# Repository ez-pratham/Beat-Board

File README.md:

# BEAT BOARD

**BEAT BOARD** is a handheld music device and synthesizer that has a cyber-retro look and feel. It is built around the dual-core **ESP32** microcontroller. It has four gold-plated touch pads that are used for finger drumming and for playing brass lead notes. It also has a 3.5" color screen that shows an audio interface in real time. There is a $2 \times 2$ control pad for master control. There is also an onboard MAX98357A I2S Class-D amplifier that powers a speaker with a cavity design.

When the **MODE** button is pressed, a menu appears on the screen. This menu allows the user to switch between a **808 Drum Machine** that has a live 16-step sequencer and a **4-Valve Acoustic Trumpet Brass Synth** that has moving valve pistons and soundwave flares!

---

## Photos & Screenshots

### Top View (Silkscreen Doodles & Controls)

### Bottom View (ROG "BEAT BOARD" & Punk Doodles)

### Schematic
  
*(Vector PDF available at [docs/images/schematic.pdf](./docs/images/schematic.pdf) | Vector SVG at [docs/images/schematic_diagram.svg](./docs/images/schematic_diagram.svg))*

### PCB Board Layout
#### Top Layer Layout (Orthogonal SPI/I2S Routing & Ground Plane)

#### Bottom Layer Layout (Power Rails & Ground Plane)

---
---

## How It Works

### How the parts fit on the console

I laid out every section of the carrier board to make the console as comfortable as possible for fast finger drumming and trumpet solos:

1. **Center Top (Display)**: A **3.5" Color TFT LCD module (480x320 SPI)** is raised at the center of the console. It shows audio waveforms, the 16-step drum sequencer grid, BPM tempo, battery status, and the interactive instrument selection menu.

2. **Center Core (Microcontroller)**: An **ESP32-WROOM-32 DevKit** microcontroller sits in female socket headers directly below the display. Its USB-C port faces downwards at the bottom edge, making firmware flashing and USB power convenient.

3. **Left Wing (Master Navigation & Drum Pads)**:
   - **Master Control Pad (Top Left)**: A $2 \times 2$ grid of tactile buttons (`UP`, `DOWN`, `SELECT`, `MODE`) lets your left thumb navigate menus, change kits, shift octaves, or mute the horn without lifting your hands.
   - **Left Touch Pads (Bottom Left)**: Two $24 \times 24\text{ mm}$ gold-plated capacitive touch pads (`PAD 1: KICK / Bb3` and `PAD 2: SNARE / D4`) are driven by two small red TTP223 daughterboards.

4. **Dedicated Top-Right Audio Bay**:
   - The **MAX98357A I2S 3W Class-D amplifier module** and green **KF301 2-pin speaker terminal block** are set in the isolated top-right corner.
   - Twisted red and black speaker wires leave cleanly from the top-right edge to a 3W cavity speaker, fully removed from your playing hands!

5. **Right Wing (100% Unobstructed Touch Controls)**:
   - The outermost elements on the right edge are `PAD 3: HI-HAT / F4` and `PAD 4: CLAP / Bb4`.
   - Your fingers and thumbs have unhindered access to the pads with zero obstacles or hurdles!

6. **Bottom Power Subsystem**:
   - Features a **TP4056 USB-C LiPo charger**, an aluminum **SPDT slide power switch**, a **JST-PH 2.0mm connector**, and a **KF301 screw terminal** for universal 3.7V LiPo battery packs.

---

## Bill of Materials (BOM)

| Item | Qty | Supplier | Cost / Item (USD) | Total Cost (USD) | Link |
| :--- | :---: | :--- | :---: | :---: | :--- |
| **ESP32 38-Pin Development Board (Dual-Core WiFi/BT)** | 1 | Robu.in | $5.35 | $5.35 | [Robu.in](https://robu.in/product/esp32-38pin-development-board-wifibluetooth-ultra-low-power-consumption-dual-core/) |
| **3.5" TFT Touch Screen Display Module** | 1 | Robu.in | $11.30 | $11.30 | [Robu.in](https://robu.in/product/3-5-inch-tft-touch-screen-module-mega-2560-r3/) |
| **Adafruit MAX98357A I2S 3W Class-D Amplifier Breakout** | 1 | Robu.in | $5.95 | $5.95 | [Robu.in](https://robu.in/product/adafruit-max98357a-i2s-3w-class-d-amplifier-breakout-board/) |
| **4Ω 40mm Diameter 3W Full-Range Audio Speaker** | 1 | Robogears | $0.81 | $0.81 | [Robogears](https://www.robogears.in/shop/012020-4ohm-40mm-diameter-3w-full-range-audio-speaker-2986) |
| **TTP223 Touch Key Sensor Modules (Pack of 2)** | 2 | Robu.in | $0.23 | $0.46 | [Robu.in](https://robu.in/product/ttp223-touch-key-module-2pcs/) |
| **6x6x5mm Tactile Push Button Switches (Pack of 10)** | 1 | Robu.in | $0.23 | $0.23 | [Robu.in](https://robu.in/product/6x6x5-tactile-push-button-switch/) |
| **TP4056 1A Li-ion Battery Charger Module (Type-C)** | 1 | Robu.in | $0.23 | $0.23 | [Robu.in](https://robu.in/product/tp4056-1a-li-ion-lithium-battery-charging-module-with-current-protection-type-c/) |
| **1250mAh PCM Protected Micro Li-Po Battery (3.7V)** | 1 | Robu.in | $5.46 | $5.46 | [Robu.in](https://robu.in/product/1250mah-pcm-protected-micro-li-po-battery/) |
| **Subminiature SPDT Slide Power Switch** | 1 | Robu.in | $0.18 | $0.18 | [Robu.in](https://robu.in/product/1-month-warranty-257/) |
| **KF301 2-Pin 5.08mm Pitch Screw Terminal Blocks (Pack of 5)** | 1 | Robu.in | $0.42 | $0.42 | [Robu.in](https://robu.in/product/kf301-2-pin-5-08mm-pitch-plug-in-screw-terminal-block-connector-pack-of-5/) |
| **JST 2-Pin Male Connector (2mm Pitch)** | 1 | Robu.in | $0.06 | $0.06 | [Robu.in](https://robu.in/product/jst-sh-2-pin-connector-2mm-pitch/) |
| **2.54mm 1x40-Pin Female Single Row Header Strips (Pack of 10)** | 1 | Robu.in | $1.43 | $1.43 | [Robu.in](https://robu.in/product/2-54mm-1x40-pin-female-single-row-header-strip-pack-of-10/) |
| **Custom BEAT BOARD Carrier PCB Manufacturing (5 pcs)** | 5 | Robu.in | $7.39 | $36.97 | [Robu.in](https://robu.in/product/online-pcb-manufacturing-service/) |
| **Total Project Cost** | **18** | — | — | **$68.85** | — |
*Downloadable spreadsheet format is available at [BOM.csv](BOM.csv).*

---

## How to Build

1. **Solder the Low-Profile Components First**:
2. **Solder Terminal Blocks & Connectors**:
3. **Solder the Female Socket Headers**:
4. **Mount the M3 Brass Standoffs**:
5. **Plug In the Modular Breakout Boards**:
6. **Connect Speaker & Battery**:

---

## Software

The firmware supports both real hardware and the Wokwi online web simulator.

### Arduino IDE Upload Instructions
1. Open the Arduino IDE.
2. In **Tools > Board**, select **ESP32 Dev Module**.
3. In **Sketch > Include Library > Manage Libraries...**, install:
   - `Adafruit GFX Library`
   - `Adafruit ILI9341` (or `Adafruit_ILI9488`)
4. Open the firmware sketch:
   - **Multi-Engine Firmware**: [firmware/music_pad_wokwi.ino](firmware/music_pad_wokwi.ino)
5. Select your COM port and hit **Upload**!

---

## KiCad & Production Files

All hardware design files are verified with KiCad 10.0 and have achieved a verified **0 DRC violation, 0 unconnected item** score:

- **KiCad Project File**: [kicad_project/music_pad.kicad_pro](kicad_project/music_pad.kicad_pro)
- **KiCad Schematic**: [kicad_project/music_pad.kicad_sch](kicad_project/music_pad.kicad_sch)
- **KiCad PCB Layout**: [kicad_project/music_pad.kicad_pcb](kicad_project/music_pad.kicad_pcb)
- **Fabrication Gerber Archive**: [gerbers.zip](gerbers.zip) *(Ready for JLCPCB, PCBWay)*
- **Bill of Materials Spreadsheet**: [BOM.csv](BOM.csv)
- **Engineering Journal**: [JOURNAL.md](JOURNAL.md)

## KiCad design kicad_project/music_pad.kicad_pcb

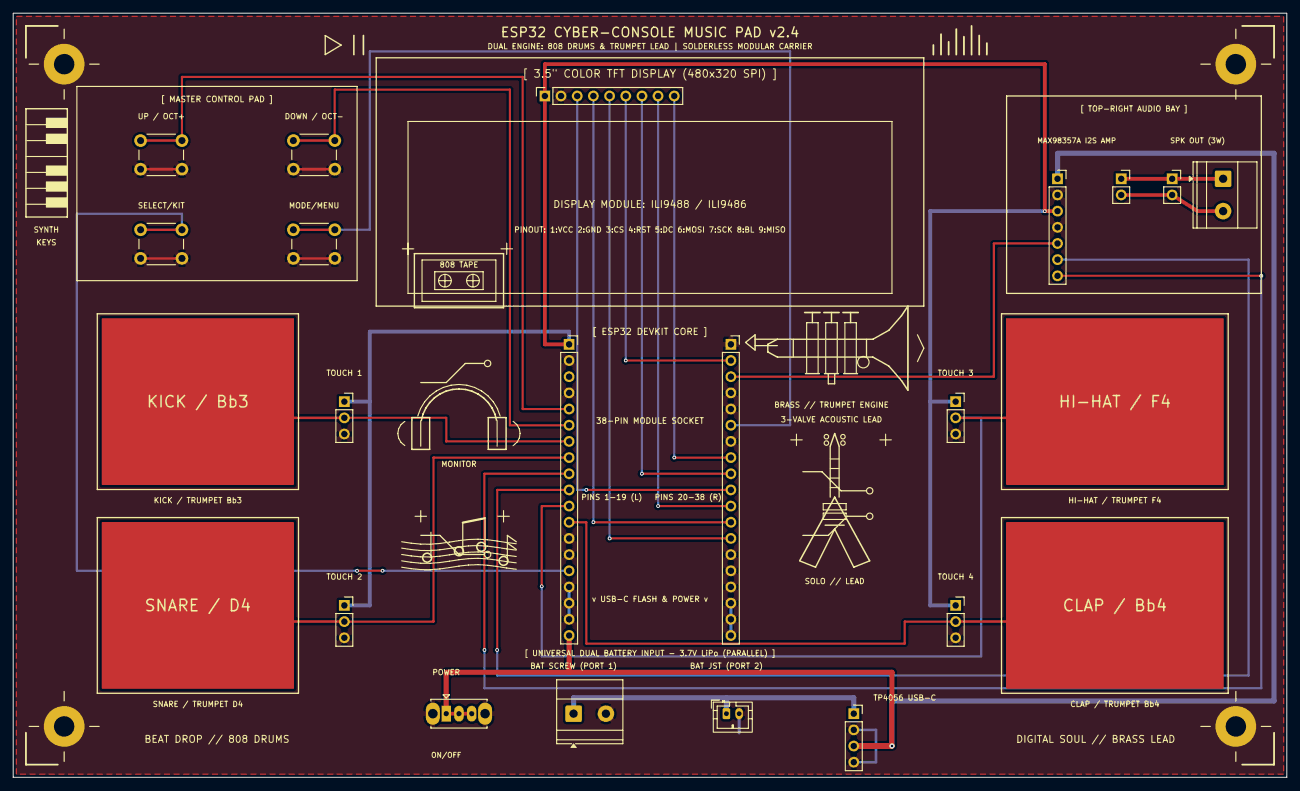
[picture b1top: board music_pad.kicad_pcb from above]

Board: 2 copper layers, 200.0 x 120.0 mm, 23 parts (0 on the bottom side), 24 nets.

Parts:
H1, H2, H3, H4: MountingHole_3.2mm_M3_Pad
J_AMP: PinSocket_1x07_P2.54mm_Vertical
J_AMP_OUT: PinSocket_1x02_P2.54mm_Vertical
J_BAT_PIN: JST_PH_B2B-PH-K_1x02_P2.00mm_Vertical
J_BAT_TERM: TerminalBlock_Phoenix_MKDS-1,5-2-5.08_1x02_P5.08m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; TerminalBlock_Phoenix_MKDS-1,5-2-5.08_1x02_P5.08mm_Horizont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
J_CHG: PinSocket_1x04_P2.54mm_Vertical
J_ESP_L: PinSocket_1x19_P2.54mm_Vertical
J_ESP_R: PinSocket_1x19_P2.54mm_Vertical
J_SPK: TerminalBlock_Phoenix_MKDS-1,5-2-5.08_1x02_P5.08m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; TerminalBlock_Phoenix_MKDS-1,5-2-5.08_1x02_P5.08mm_Horizont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
J_SPK_HDR: PinSocket_1x02_P2.54mm_Vertical
J_TFT: PinSocket_1x09_P2.54mm_Vertical
J_TP1, J_TP2, J_TP3, J_TP4: PinSocket_1x03_P2.54mm_Vertical
SW1, SW2, SW3, SW4: SW_PUSH_6mm
SW_PWR: SW_Slide_SPDT_Straight_CK_OS102011MS2Q

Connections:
+3V3: J_AMP.3, J_ESP_L.1, J_TFT.1, J_TP1.1, J_TP2.1, J_TP3.1, J_TP4.1
+5V_SYS: J_AMP.1, J_CHG.3, J_ESP_L.19, SW_PWR.1, SW_PWR.2, SW_PWR.3
GND: H1.1, H2.1, H3.1, H4.1, J_AMP.2, J_AMP.4, J_BAT_PIN.2, J_BAT_TERM.2, J_CHG.2, J_CHG.4, J_ESP_L.2, J_ESP_L.4, J_ESP_L.13, J_ESP_L.14, J_ESP_L.16, J_ESP_L.17, J_ESP_L.18, J_ESP_R.1, J_ESP_R.4, J_ESP_R.5, J_ESP_R.7, J_ESP_R.14, J_ESP_R.15, J_ESP_R.16, J_ESP_R.17, J_ESP_R.18, J_ESP_R.19, J_TFT.2, J_TP1.3, J_TP2.3, J_TP3.3, J_TP4.3, SW1.2, SW2.2, SW3.2, SW4.2
I2S_BCLK: J_AMP.6, J_ESP_L.10
I2S_DOUT: J_AMP.5, J_ESP_R.3
I2S_LRCK: J_AMP.7, J_ESP_L.9
NAV_DOWN: J_ESP_L.6, SW2.1
NAV_MODE: J_ESP_R.6, SW4.1
NAV_SELECT: J_ESP_L.15, SW3.1
NAV_UP: J_ESP_L.5, SW1.1
SPK_N: J_AMP_OUT.2, J_SPK.2, J_SPK_HDR.2
SPK_P: J_AMP_OUT.1, J_SPK.1, J_SPK_HDR.1
TFT_BL: J_ESP_R.11, J_TFT.8
TFT_CS: J_ESP_R.10, J_TFT.3
TFT_DC: J_ESP_R.13, J_TFT.5
TFT_MISO: J_ESP_R.8, J_TFT.9
TFT_MOSI: J_ESP_R.2, J_TFT.6
TFT_RST: J_ESP_R.12, J_TFT.4
TFT_SCK: J_ESP_R.9, J_TFT.7
TP1_OUT: J_ESP_L.7, J_TP1.2
TP2_OUT: J_ESP_L.8, J_TP2.2
TP3_OUT: J_ESP_L.11, J_TP3.2
TP4_OUT: J_ESP_L.12, J_TP4.2
V_BAT: J_BAT_PIN.1, J_BAT_TERM.1, J_CHG.1
